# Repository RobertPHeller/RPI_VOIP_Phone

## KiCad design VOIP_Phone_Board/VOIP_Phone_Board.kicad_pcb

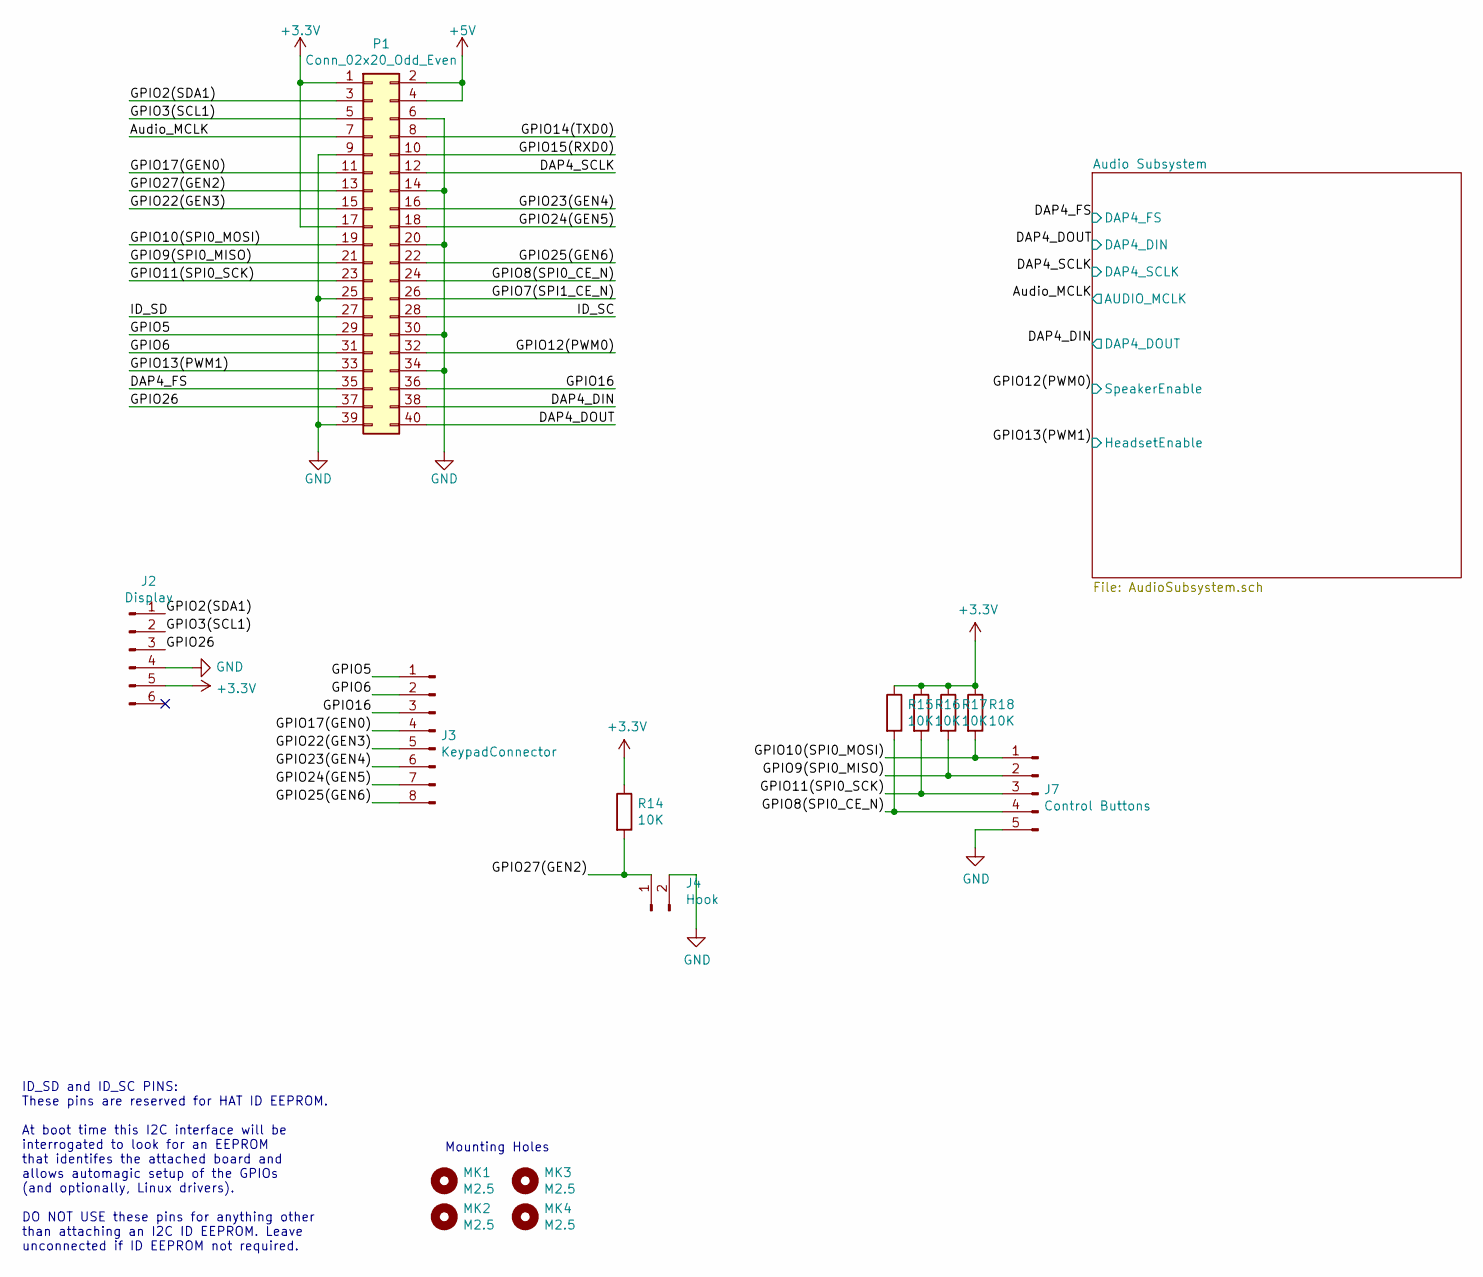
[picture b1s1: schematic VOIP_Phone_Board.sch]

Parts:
J2: Display; PinHeader_1x06_P2.54mm_Vertical
J3: KeypadConnector; PinHeader_1x08_P2.54mm_Vertical
J4: Hook; PinHeader_1x02_P2.54mm_Vertical
J7: Control Buttons; PinHeader_1x05_P2.54mm_Vertical
MK1, MK2, MK3, MK4: M2.5; MountingHole_2.7mm_M2.5
P1: Conn_02x20_Odd_Even; PinSocket_2x20_P2.54mm_Vertical
R14, R15, R16, R17, R18: 10K; R_0603_1608Metric_Pad1.05x0.95mm_HandSolder; Mouser Part Number 603-AC0603DR-0710KL

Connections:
+3V3: J2.5, P1.1, P1.17, R14.1, R15.1, R16.1, R17.1, R18.1; also elsewhere on the board
+5V: P1.2, P1.4; also elsewhere on the board
/Audio_MCLK: P1.7; also elsewhere on the board
/DAP4_DIN: P1.38; also elsewhere on the board
/DAP4_DOUT: P1.40; also elsewhere on the board
/DAP4_FS: P1.35; also elsewhere on the board
/DAP4_SCLK: P1.12; also elsewhere on the board
/GPIO2(SDA1): J2.1, P1.3
/GPIO3(SCL1): J2.2, P1.5
/GPIO5: J3.1 (Column_4), P1.29
/GPIO6: J3.2 (Column_3), P1.31
/GPIO7(SPI1_CE_N): P1.26
/GPIO8(SPI0_CE_N): J7.4, P1.24, R15.2
/GPIO9(SPI0_MISO): J7.2, P1.21, R17.2
/GPIO10(SPI0_MOSI): J7.1, P1.19, R18.2
/GPIO11(SPI0_SCK): J7.3, P1.23, R16.2
/GPIO12(PWM0): P1.32; also elsewhere on the board
/GPIO13(PWM1): P1.33; also elsewhere on the board
/GPIO14(TXD0): P1.8
/GPIO15(RXD0): P1.10
/GPIO16: J3.3 (Column_2), P1.36
/GPIO17(GEN0): J3.4 (Column_1), P1.11
/GPIO22(GEN3): J3.5 (Row_4), P1.15
/GPIO23(GEN4): J3.6 (Row_3), P1.16
/GPIO24(GEN5): J3.7 (Row_2), P1.18
/GPIO25(GEN6): J3.8 (Row_1), P1.22
/GPIO26: J2.3, P1.37
/GPIO27(GEN2): J4.1, P1.13, R14.2
/ID_SC: P1.28
/ID_SD: P1.27
GND: J2.4, J4.2, J7.5, P1.6, P1.9, P1.14, P1.20, P1.25, P1.30, P1.34, P1.39; also elsewhere on the board

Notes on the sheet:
ID_SD and ID_SC PINS: These pins are reserved for HAT ID EEPROM. At boot time this I2C interface will be interrogated to look for an EEPROM that identifes the attached board and allows automagic setup of the GPIOs (and optionally, Linux drivers). DO NOT USE these pins for anything other than attach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
Mounting Holes

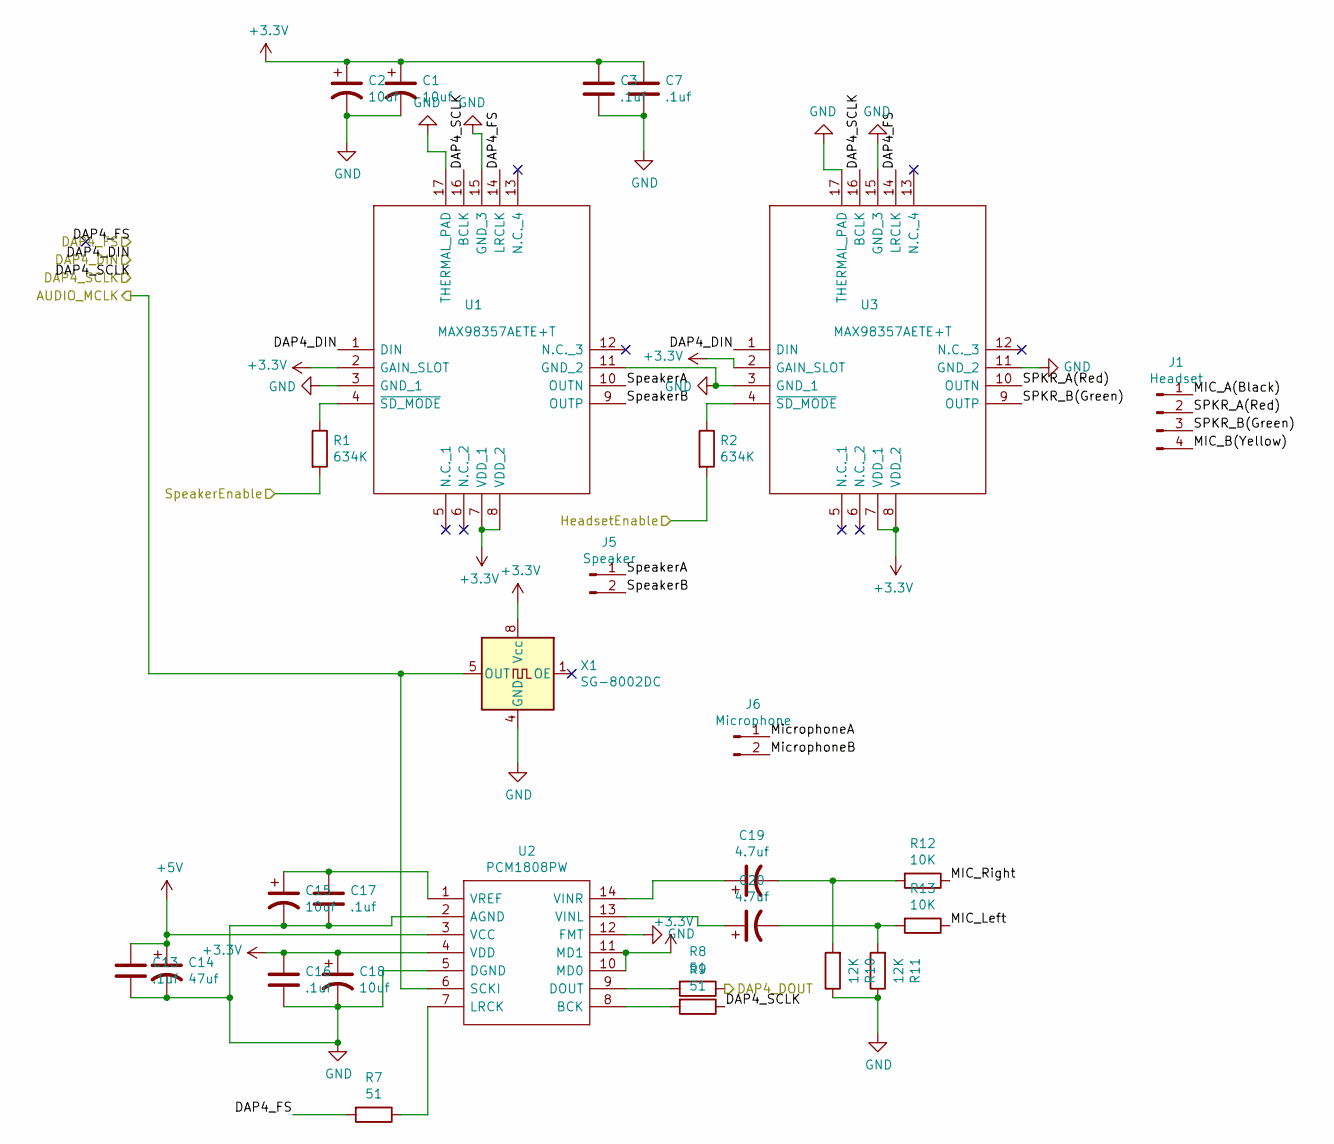
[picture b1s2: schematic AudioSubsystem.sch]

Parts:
C1, C2, C15, C18: 10uf; CP_0603_1608Metric_Pad1.05x0.95mm_HandSolder; Mouser Part Number 647-F981A106MMA
C3, C7, C13, C16, C17: .1uf; C_0603_1608Metric_Pad1.05x0.95mm_HandSolder; Mouser Part Number 80-C603C104K5RAC3121
C14: 47uf; CP_Radial_D6.3mm_P2.50mm; Mouser Part Number 140-REA470M1HBK0611P
C19, C20: 4.7uf; CP_0603_1608Metric_Pad1.05x0.95mm_HandSolder; Mouser Part Number 647-F981A475MMA
J1: Headset; PinHeader_1x04_P2.54mm_Vertical
J5: Speaker; PinHeader_1x02_P2.54mm_Vertical
J6: Microphone; PinHeader_1x02_P2.54mm_Vertical
R1, R2: 634K; R_0603_1608Metric_Pad1.05x0.95mm_HandSolder; Mouser Part Number 603-RT0603FRE07634KL
R7, R8, R9: 51; R_0603_1608Metric_Pad1.05x0.95mm_HandSolder; Mouser Part Number 667-ERJ-PA3J510V
R10, R11: 12K; R_0603_1608Metric_Pad1.05x0.95mm_HandSolder; Mouser Part Number 603-AC0603JR-0712KL
R12, R13: 10K; R_0603_1608Metric_Pad1.05x0.95mm_HandSolder; Mouser Part Number 603-AC0603DR-0710KL
U1, U3: MAX98357AETE+T; QFN50P300X300X80-17N; Mouser Part Number 700-MAX98357AETE+T
U2: PCM1808PW; SOP65P640X120-14N; Mouser Part Number 595-PCM1808PW
X1: SG-8002DC; Oscillator_SeikoEpson_SG-8002DC; Mouser Part Number 732-SG-8002DC6.144R

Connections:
+3V3: C1.1, C2.1, C3.1, C7.1, C16.1, C18.1, U1.2 (GAIN_SLOT), U1.7 (VDD_1), U1.8 (VDD_2), U2.4 (VDD), U2.10 (MD0), U2.11 (MD1), U3.2 (GAIN_SLOT), U3.7 (VDD_1), U3.8 (VDD_2), X1.8 (Vcc); also elsewhere on the board
+5V: C13.1, C14.1, U2.3 (VCC); also elsewhere on the board
/Audio Subsystem/MIC_A(Black): J1.1
/Audio Subsystem/MIC_B(Yellow): J1.4
/Audio Subsystem/MIC_Left: R13.1
/Audio Subsystem/MIC_Right: R12.1
/Audio Subsystem/MicrophoneA: J6.1
/Audio Subsystem/MicrophoneB: J6.2
/Audio Subsystem/SPKR_A(Red): J1.2, U3.10 (OUTN)
/Audio Subsystem/SPKR_B(Green): J1.3, U3.9 (OUTP)
/Audio Subsystem/SpeakerA: J5.1, U1.10 (OUTN)
/Audio Subsystem/SpeakerB: J5.2, U1.9 (OUTP)
/Audio_MCLK: U2.6 (SCKI), X1.5 (OUT); also elsewhere on the board
/DAP4_DIN: R8.1; also elsewhere on the board
/DAP4_DOUT: U1.1 (DIN), U3.1 (DIN); also elsewhere on the board
/DAP4_FS: R7.2, U1.14 (LRCLK), U3.14 (LRCLK); also elsewhere on the board
/DAP4_SCLK: R9.1, U1.16 (BCLK), U3.16 (BCLK); also elsewhere on the board
/GPIO12(PWM0): R1.2; also elsewhere on the board
/GPIO13(PWM1): R2.2; also elsewhere on the board
GND: C1.2, C2.2, C3.2, C7.2, C13.2, C14.2, C15.2, C16.2, C17.2, C18.2, R10.1, R11.1, U1.3 (GND_1), U1.11 (GND_2), U1.15 (GND_3), U1.17 (THERMAL_PAD), U2.2 (AGND), U2.5 (DGND), U2.12 (FMT), U3.3 (GND_1), U3.11 (GND_2), U3.15 (GND_3), U3.17 (THERMAL_PAD), X1.4 (GND); also elsewhere on the board
unnamed: C15.1, C17.1, U2.1 (VREF)
unnamed: C19.1, U2.14 (VINR)
unnamed: C19.2, R10.2, R12.2
unnamed: C20.1, U2.13 (VINL)
unnamed: C20.2, R11.2, R13.2
unnamed: R1.1, U1.4 (~SD_MODE)
unnamed: R2.1, U3.4 (~SD_MODE)
unnamed: R7.1, U2.7 (LRCK)
unnamed: R8.2, U2.9 (DOUT)
unnamed: R9.2, U2.8 (BCK)

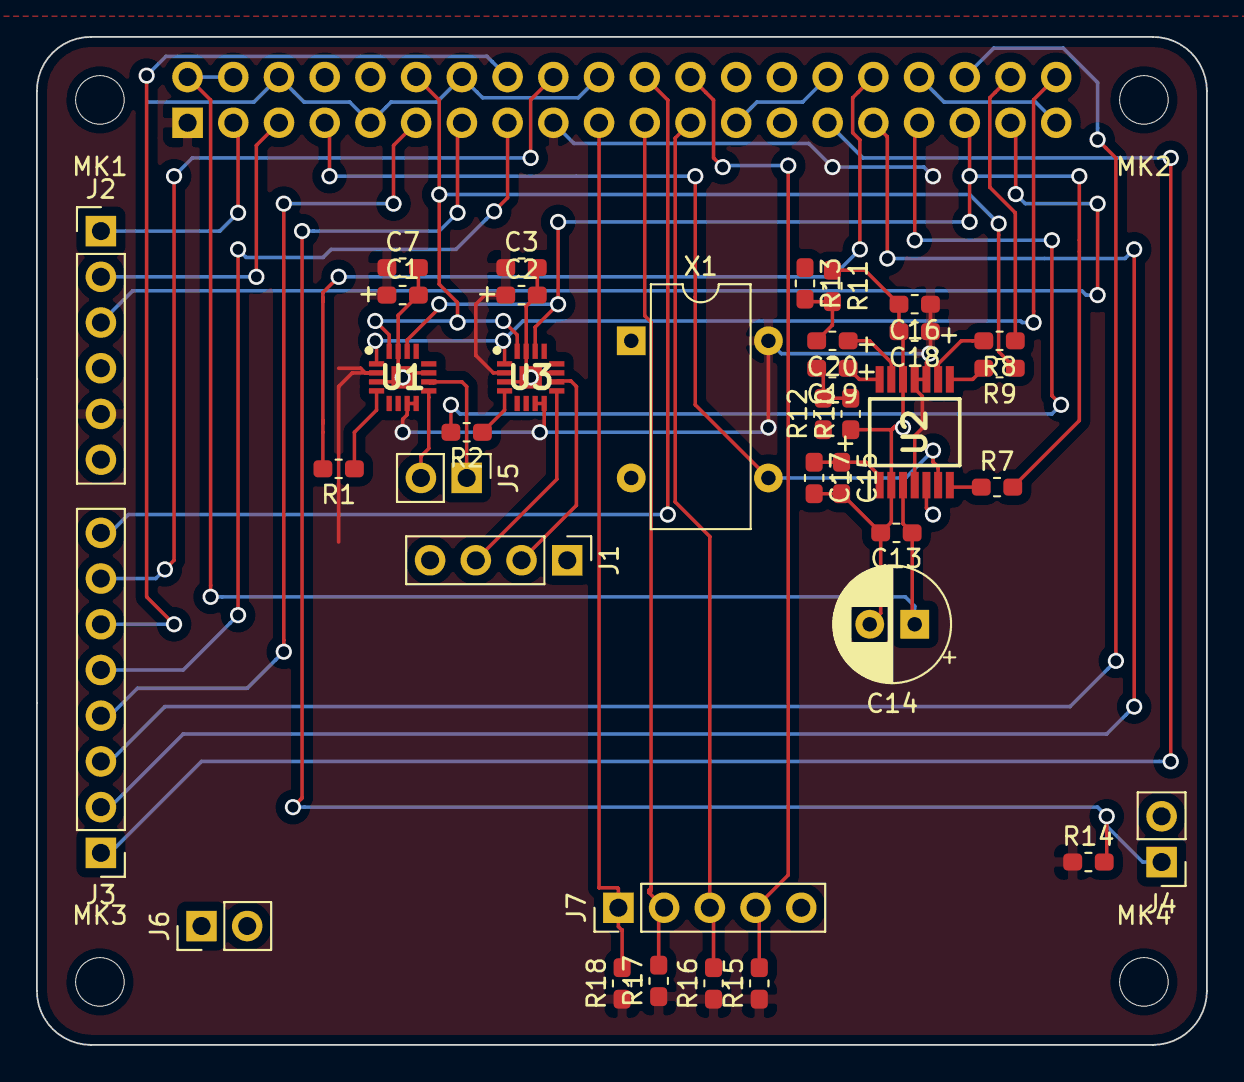
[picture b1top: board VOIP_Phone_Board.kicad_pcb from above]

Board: 2 copper layers, 65.0 x 56.0 mm, 42 parts (1 on the bottom side), 40 nets.

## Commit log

2022-04-10 Audio output stage mostly done.
2022-04-10 Started on the audio input section.
2022-04-11 Completed audio input section.
2022-04-11 Add in DCM file.
2022-04-11 Add .gitignore
2022-04-11 Add keypad.
2022-04-11 Add Hook Switch.
2022-04-11 Complete all I/O and connectors.
2022-04-11 Amplifiers notes.
2022-04-12 flush
2022-04-12 MAX98357A Version.
2022-04-12 Started with ADAU1361.
